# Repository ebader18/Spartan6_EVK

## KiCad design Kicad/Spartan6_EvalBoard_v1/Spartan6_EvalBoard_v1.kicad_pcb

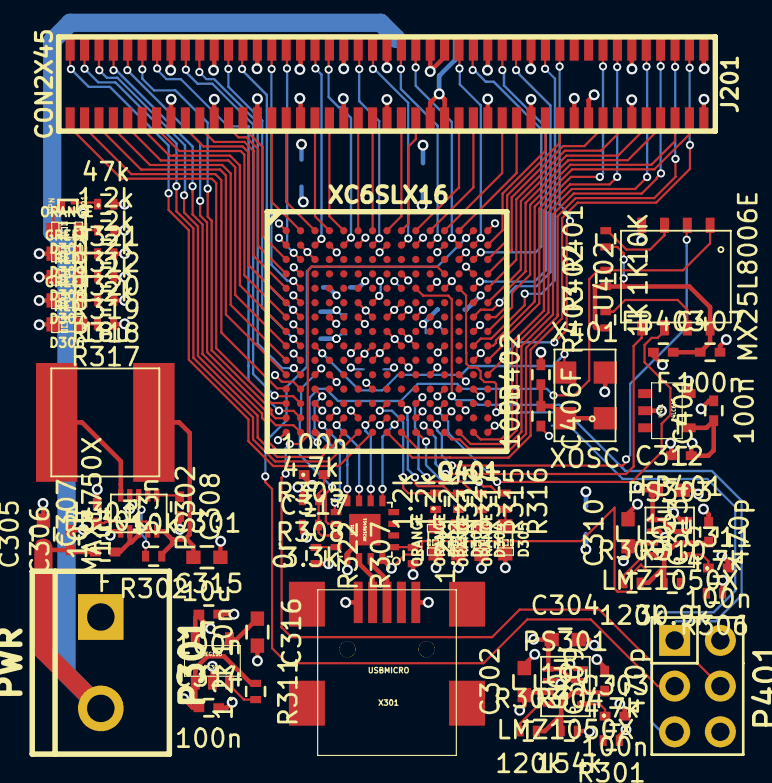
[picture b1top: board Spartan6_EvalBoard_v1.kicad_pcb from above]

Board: 4 copper layers, 84 parts (0 on the bottom side), 125 nets.

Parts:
C301, C302, C304, C305, C310, C312, C413, C414: 10u; C_0603
C303, C311, C314, C315, C317, C401, C406, C407: 100n; C_0402
C306, C307: 1u; C_0402
C308: 3.3n; C_0402
C309, C313: 470p; C_0402
C316: 10n; C_0603
C402, C403, C411, C412: 4.7u; C_0603
C405, C408, C409, C410: 470n; C_0402
D201: DIODESCH; SOD-123FL
D301, D302, D303, D304, D305: ORANGE; LED-0603
D306, D308: RED; LED-0603
D307, D309: GREEN; LED-0603
FB301, FB401, FB402, FB403: F; C_0402
J201: CON2X45; CON45X2
L301: 18u; IND6x6
P301: PWR; bornier2
P401: CONN_3X2; Pin_Header_Straight_2x03
PS301, PS303: LMZ1050X; SIL08
PS302: MAX1750X; TDFN10
PS304: REG113; SOT23-5
Q301: NPN; TSLP-3-1
Q401: XC6SLX16; CSG225
R301, R306, R308: 4.7k; R_0402
R302: 10k; R_0402
R303, R309: 120k; R_0402
R304: 154k; R_0402
R305: 3.3k; R_0402
R307, R311, R312, R313, R314, R315, R316, R317, R318, R319, R320: 1.2k; R_0402
R310: 30.9k; R_0402
R321: 47k; R_0402
R322: 0r; R_0402
R401: 10K; R_0402
R402, R403: 1K; R_0402
U301: XR21B1411; QFN-16
U401: 24LC64T; SOT23-5
U402: MX25L8006E; WSON8
X301: USBMICRO; USB-MINI-B-SMD
X401: XOSC; XTAL5032

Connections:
1.2V: C312.1, C402.1, C403.1, C405.1, J201.73, PS303.3, PS303.5, Q401.F9, Q401.G6, Q401.G8, Q401.H9, Q401.J8, Q401.J10, Q401.K7, R321.1
3.3V: C304.1, C408.1, C409.1, C410.1, C411.1, C412.1, C413.1, C414.1, FB401.2, FB402.2, FB403.1, J201.72, J201.74, P401.2, PS301.3, PS301.5, Q401.B1, Q401.B4, Q401.B8, Q401.B12, Q401.D2, Q401.D9, Q401.D14, Q401.E12, Q401.F7, Q401.G4, Q401.G10, Q401.H2, Q401.H14, Q401.J6, Q401.J12, Q401.K9, Q401.L4, Q401.M2, Q401.M7, Q401.M12, Q401.M14, Q401.P4, Q401.P8, Q401.P12, R320.1
5V: C301.1, C302.1, C310.1, J201.52, J201.54, L301.2, PS301.7, PS302.5, PS303.7, R301.1, R302.1, R306.1, R312.1, R319.1
/IO Connector/IO1: J201.1, Q401.N1
/IO Connector/IO2: J201.2, Q401.R7
/IO Connector/IO3: J201.3, Q401.M1
/IO Connector/IO4: J201.4, Q401.R6
/IO Connector/IO5: J201.5, Q401.L1
/IO Connector/IO6: J201.6, Q401.R5
/IO Connector/IO7: J201.7, Q401.K1
/IO Connector/IO8: J201.8, Q401.R4
/IO Connector/IO9: J201.9, Q401.J1
/IO Connector/IO10: J201.10, Q401.R2
/IO Connector/IO11: J201.11, Q401.H1
/IO Connector/IO12: J201.12, Q401.P1
/IO Connector/IO13: J201.13, Q401.G1
/IO Connector/IO14: J201.14, Q401.P2
/IO Connector/IO17: J201.17, Q401.F1
/IO Connector/IO18: J201.18, Q401.N2
/IO Connector/IO19: J201.19, Q401.E1
/IO Connector/IO20: J201.20, Q401.L2
/IO Connector/IO23: J201.23, Q401.D1
/IO Connector/IO24: J201.24, Q401.J2
/IO Connector/IO25: J201.25, Q401.C1
/IO Connector/IO26: J201.26, Q401.G2
/IO Connector/IO29: J201.29, Q401.A2
/IO Connector/IO30: J201.30, Q401.E2
/IO Connector/IO31: J201.31, Q401.A3
/IO Connector/IO32: J201.32, Q401.C2
/IO Connector/IO35: J201.35, Q401.A4
/IO Connector/IO36: J201.36, Q401.B3
/IO Connector/IO37: J201.37, Q401.A5
/IO Connector/IO38: J201.38, Q401.B5
/IO Connector/IO41: J201.41, Q401.A6
/IO Connector/IO42: J201.42, Q401.B7
/IO Connector/IO43: J201.43, Q401.A7
/IO Connector/IO44: J201.44, Q401.B9
/IO Connector/IO47: J201.47, Q401.A8
/IO Connector/IO48: J201.48, Q401.B11
/IO Connector/IO49: J201.49, Q401.A9
/IO Connector/IO50: J201.50, Q401.B13
/IO Connector/IO55: J201.55, Q401.A10
/IO Connector/IO56: J201.56, Q401.B14
/IO Connector/IO57: J201.57, Q401.A11
/IO Connector/IO58: J201.58, Q401.C14
/IO Connector/IO61: J201.61, Q401.A12
/IO Connector/IO62: J201.62, Q401.E14
/IO Connector/IO63: J201.63, Q401.A13
/IO Connector/IO64: J201.64, Q401.G14
/IO Connector/IO67: J201.67, Q401.B15
/IO Connector/IO68: J201.68, Q401.J14
/IO Connector/IO69: J201.69, Q401.C15
/IO Connector/IO70: J201.70, Q401.L15
/IO Connector/IO75: J201.75, Q401.D15
/IO Connector/IO76: J201.76, Q401.K15
/IO Connector/IO77: J201.77, Q401.E15
/IO Connector/IO78: J201.78, Q401.R14
/IO Connector/IO81: J201.81, Q401.F15
/IO Connector/IO82: J201.82, Q401.R13
/IO Connector/IO83: J201.83, Q401.G15
/IO Connector/IO84: J201.84, Q401.R12
/IO Connector/IO85: J201.85, Q401.H15
/IO Connector/IO86: J201.86, Q401.R9
/IO Connector/IO87: J201.87, Q401.J15
/IO Connector/IO88: J201.88, Q401.R8
/IO Connector/VCC_OUT: D201.2, J201.51, J201.53
/POWER/3.3V_USB: C315.1, PS304.5, R318.1, R322.2
/POWER/5V_SW_RDY: PS302.8, R302.2
/POWER/5V_USB: C314.1, PS304.1, R305.1, R311.1, R317.1, U301.16, X301.1
/POWER/LED1: Q401.N8, R313.1
/POWER/LED2: Q401.N9, R314.1
/POWER/LED3: Q401.N10, R315.1
/POWER/LED4: Q401.R10, R316.1
/POWER/PC_GPIO0: Q401.P3, U301.8
/POWER/PC_GPIO1: Q401.P5, U301.7
/POWER/PC_GPIO2: Q401.P7, U301.6
/POWER/PC_GPIO3: Q401.P9, U301.5
/POWER/PC_RX: Q401.L3, U301.10
/POWER/PC_TX: Q401.M3, U301.9
/POWER/USBD+: U301.15, X301.3
/POWER/USBD-: U301.14, X301.2
/SPARTAN6/CLK: Q401.J3, X401.3
/SPARTAN6/FLASH_CSn: Q401.R3, R402.2, U402.1
/SPARTAN6/FLASH_MISO: Q401.P11, U402.2
/SPARTAN6/FLASH_MOSI: Q401.R11, U402.5
/SPARTAN6/FLASH_SCK: Q401.N12, U402.6
/SPARTAN6/I2C_EE_SCL: Q401.N14, U401.1
/SPARTAN6/I2C_EE_SDA: Q401.M15, U401.3
/SPARTAN6/TCK: P401.3, Q401.A14
/SPARTAN6/TDI: P401.1, Q401.E10
/SPARTAN6/TDO: P401.4, Q401.D12
/SPARTAN6/TMS: P401.5, Q401.E13
GND: C301.2, C302.2, C303.2, C304.2, C305.2, C306.2, C307.2, C308.2, C309.2, C310.2, C311.2, C312.2, C313.2, C314.2, C315.2, C316.2, C317.2, C401.2, C402.2, C403.2, C405.2, C406.2, C407.2, C408.2, C409.2, C410.2, C411.2, C412.2, C413.2, C414.2, D302.2, D303.2, D304.2, D305.2, D306.2, D307.2, D308.2, D309.2, J201.15, J201.16, J201.21, J201.22, J201.27, J201.28, J201.33, J201.34, J201.39, J201.40, J201.45, J201.46, J201.59, J201.60, J201.65, J201.66, J201.71, J201.79, J201.80, J201.89, J201.90, P301.1, P401.6, PS301.4, PS301.6, PS302.1, PS302.9, PS303.4, PS303.6, PS304.2, Q301.1, Q401.A1, Q401.A15, Q401.B2, Q401.B6, Q401.B10, Q401.C3, Q401.C13, Q401.E11, Q401.F2, Q401.F6, Q401.F14, Q401.G7, Q401.G9, Q401.H8, Q401.J7, Q401.J9, Q401.K2, Q401.K6, Q401.K14, Q401.L11, Q401.L13, Q401.N3, Q401.N13, Q401.P6, Q401.P10, Q401.R1, Q401.R15, R304.2, R307.1, R308.2, R310.2, U301.13, U301.17, U401.2, U401.5, U402.4, X301.5, X401.2
unnamed: C303.1, PS301.1, R301.2
unnamed: C307.1, PS302.4
unnamed: C308.1, PS302.6
unnamed: C309.1, PS301.2, R303.2, R304.1
unnamed: C311.1, PS303.1, R306.2
unnamed: C313.1, PS303.2, R309.2, R310.1
unnamed: C316.1, PS304.4
unnamed: C317.1, R305.2, R308.1, U301.11
unnamed: C401.1, FB401.1, U401.4
unnamed: C406.1, FB402.1, X401.1, X401.4
unnamed: C407.1, FB403.2, R401.1, R402.1, R403.1, U402.8
unnamed: D301.1, R312.2
unnamed: D301.2, Q301.3
unnamed: D302.1, R313.2
unnamed: D303.1, R314.2
unnamed: D304.1, R315.2
unnamed: D305.1, R316.2
unnamed: D306.1, R317.2
unnamed: D307.1, R318.2
unnamed: D308.1, R319.2
unnamed: D309.1, R320.2
unnamed: FB301.2, PS302.2, PS302.3
unnamed: L301.1, PS302.10
unnamed: PS301.8, R303.1
unnamed: PS303.8, R309.1
unnamed: PS304.3, R311.2
unnamed: Q301.2, R321.2
unnamed: R307.2, U301.1
unnamed: R322.1, U301.12
unnamed: R401.2, U402.3
unnamed: R403.2, U402.7
VCC: C305.1, C306.1, D201.1, FB301.1, P301.2

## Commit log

2014-10-01 Schematic almost done
    Schematic almost done, just to connect connector to FPGA
2014-10-02 Schematic and netllist created
    The correct fpga connection to connector will have to be carried out.
    Some more footprints need to be created.
2014-10-27 Schematic completed, layout starte
    Schematic completed, layout starte
2014-11-01 BZR - Layout half done
    Using LaunchPad Kicad
    Layout more than half completed
2014-11-03 Layout completed, just need to run DRC.
